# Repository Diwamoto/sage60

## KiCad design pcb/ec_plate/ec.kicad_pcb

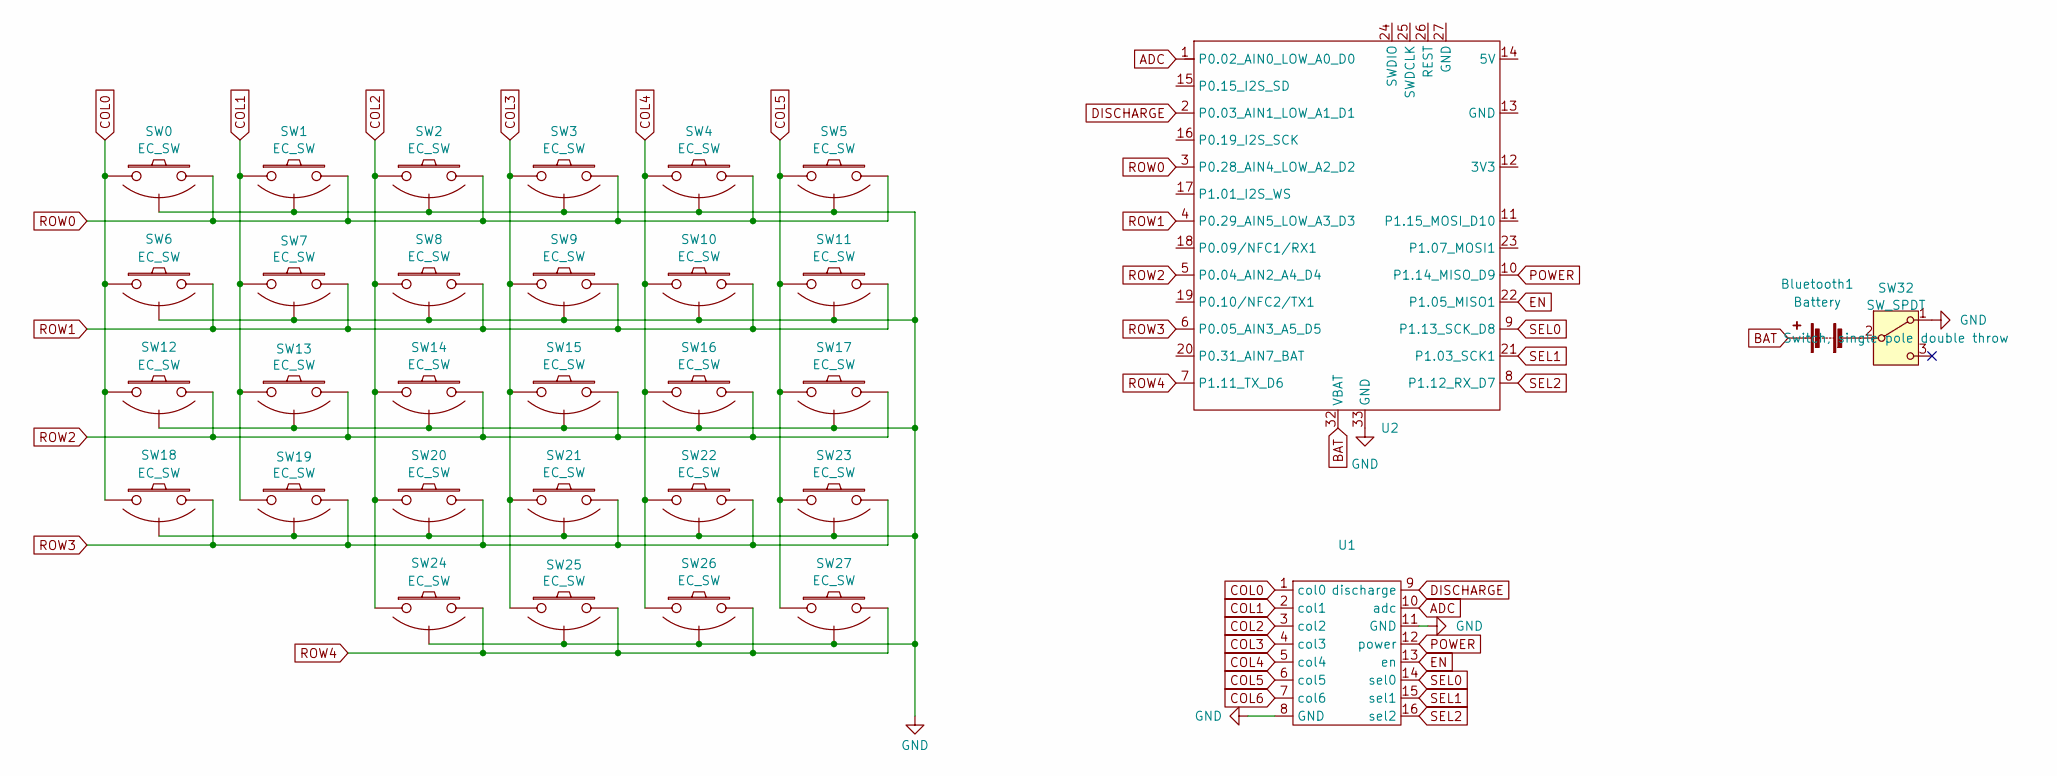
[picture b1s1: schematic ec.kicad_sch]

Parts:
Bluetooth1: Battery
SW0, SW1, SW2, SW3, SW4, SW5, SW6, SW7, SW8, SW9, SW10, SW11, SW12, SW13, SW14, SW15, SW16, SW17, SW18, SW19, SW20, SW21, SW22, SW23, SW24, SW25, SW26, SW27: EC_SW; ecs_pad_1U_no_ring
SW32: SW_SPDT; PinHeader_1x03_P2.54mm_Vertical
U1: ec_scan_module
U2: XIAO-nRF52840-Plus-DIP

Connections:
ADC: U1.10 (adc), U2.1 (P0.02_AIN0_LOW_A0_D0); also elsewhere on the board
COL0: SW0.1, SW6.1, SW12.1, SW18.1, U1.1 (col0)
COL1: SW1.1, SW7.1, SW13.1, SW19.1, U1.2 (col1)
COL2: SW2.1, SW8.1, SW14.1, SW20.1, SW24.1, U1.3 (col2)
COL3: SW3.1, SW9.1, SW15.1, SW21.1, SW25.1, U1.4 (col3)
COL4: SW4.1, SW10.1, SW16.1, SW22.1, SW26.1, U1.5 (col4)
COL5: SW5.1, SW11.1, SW17.1, SW23.1, SW27.1, U1.6 (col5)
COL6: U1.7 (col6)
DISCHARGE: U1.9 (discharge), U2.2 (P0.03_AIN1_LOW_A1_D1); also elsewhere on the board
EN: U1.13 (en), U2.22 (P1.05_MISO1); also elsewhere on the board
GND: SW0.3 (SG), SW1.3 (SG), SW2.3 (SG), SW3.3 (SG), SW4.3 (SG), SW5.3 (SG), SW6.3 (SG), SW7.3 (SG), SW8.3 (SG), SW9.3 (SG), SW10.3 (SG), SW11.3 (SG), SW12.3 (SG), SW13.3 (SG), SW14.3 (SG), SW15.3 (SG), SW16.3 (SG), SW17.3 (SG), SW18.3 (SG), SW19.3 (SG), SW20.3 (SG), SW21.3 (SG), SW22.3 (SG), SW23.3 (SG), SW24.3 (SG), SW25.3 (SG), SW26.3 (SG), SW27.3 (SG), SW32.1 (A), U1.8 (GND), U1.11 (GND), U2.33 (GND); also elsewhere on the board
unnamed: Bluetooth1.1 (+), U2.32 (VBAT)
unnamed: Bluetooth1.2 (-), SW32.2 (B)
POWER: U1.12 (power), U2.10 (P1.14_MISO_D9); also elsewhere on the board
ROW0: SW0.2, SW1.2, SW2.2, SW3.2, SW4.2, SW5.2, U2.3 (P0.28_AIN4_LOW_A2_D2); also elsewhere on the board
ROW1: SW6.2, SW7.2, SW8.2, SW9.2, SW10.2, SW11.2, U2.4 (P0.29_AIN5_LOW_A3_D3); also elsewhere on the board
ROW2: SW12.2, SW13.2, SW14.2, SW15.2, SW16.2, SW17.2, U2.5 (P0.04_AIN2_A4_D4); also elsewhere on the board
ROW3: SW18.2, SW19.2, SW20.2, SW21.2, SW22.2, SW23.2, U2.6 (P0.05_AIN3_A5_D5); also elsewhere on the board
ROW4: SW24.2, SW25.2, SW26.2, SW27.2, U2.7 (P1.11_TX_D6); also elsewhere on the board
SEL0: U1.14 (sel0), U2.9 (P1.13_SCK_D8); also elsewhere on the board
SEL1: U1.15 (sel1), U2.21 (P1.03_SCK1); also elsewhere on the board
SEL2: U1.16 (sel2), U2.8 (P1.12_RX_D7); also elsewhere on the board

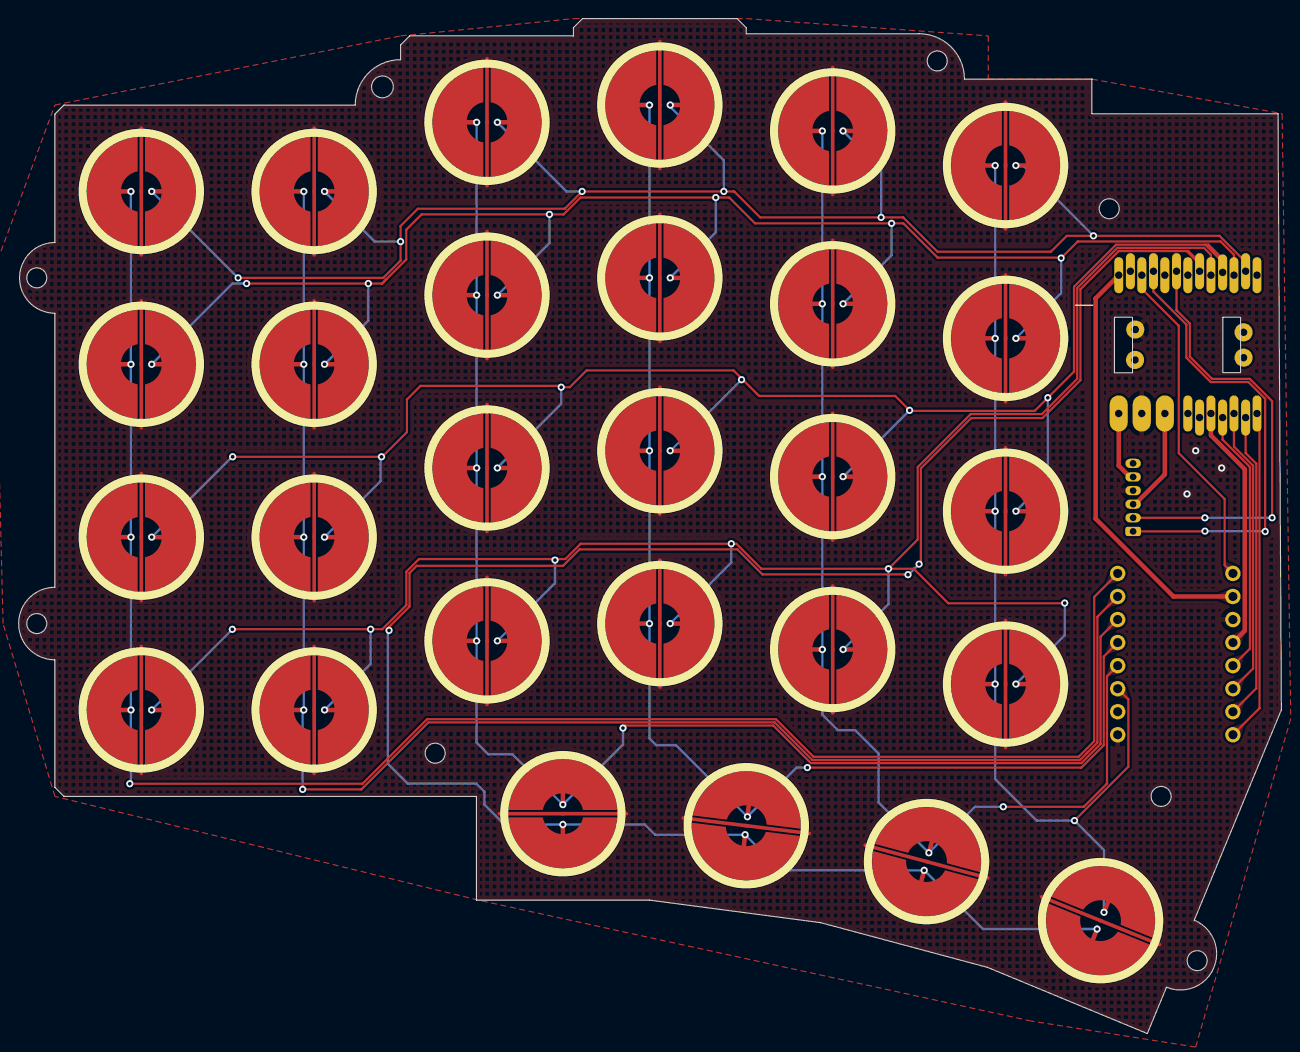
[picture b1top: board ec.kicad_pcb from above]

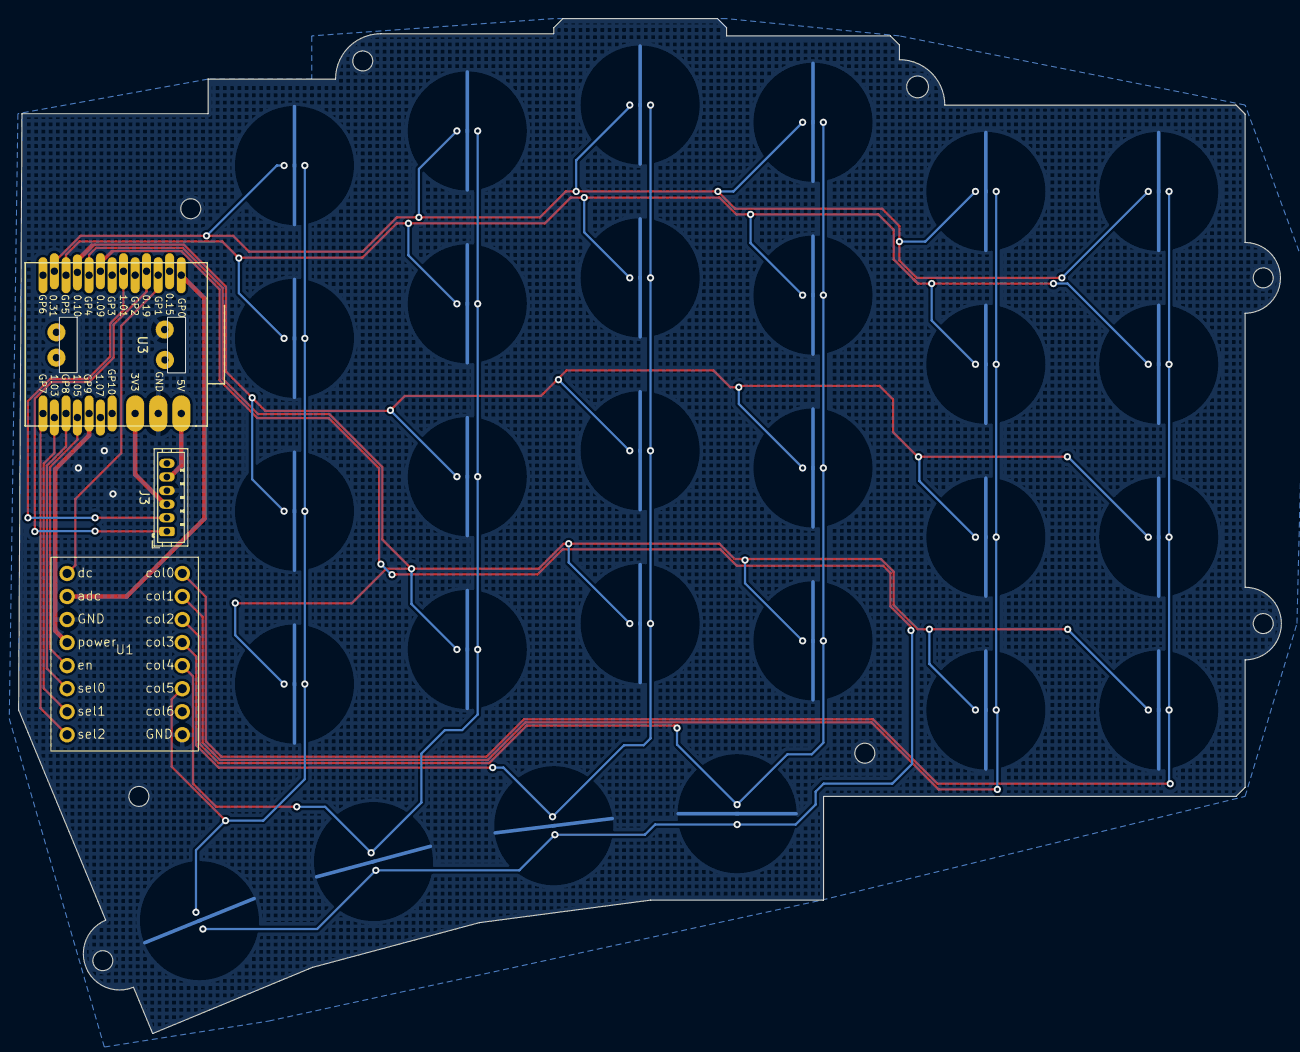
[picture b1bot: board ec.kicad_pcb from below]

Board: 2 copper layers, 139.2 x 111.9 mm, 31 parts (2 on the bottom side), 23 nets.

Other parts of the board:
J3: Conn_01x06_Socket; JST_ZH_B6B-ZR_1x06_P1.50mm_Vertical
U3: XIAO_nRF52840_plus_mki

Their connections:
+3.3V: J3.3, U3.12 (3V3)
ADC: U3.1 (P0.02_AIN0_LOW_A0_D0); also elsewhere on the board
DISCHARGE: U3.2 (P0.03_AIN1_LOW_A1_D1); also elsewhere on the board
EN: U3.24 (SWDIO); also elsewhere on the board
GND: J3.4, U3.13 (GND), U3.27 (GND); also elsewhere on the board
POWER: U3.10 (P1.14_MISO_D9); also elsewhere on the board
ROW0: U3.22 (P1.05_MISO1); also elsewhere on the board
ROW1: U3.6 (P0.05_AIN3_A5_D5); also elsewhere on the board
ROW2: U3.21 (P1.03_SCK1); also elsewhere on the board
ROW3: U3.5 (P0.04_AIN2_A4_D4); also elsewhere on the board
ROW4: U3.20 (P0.31_AIN7_BAT); also elsewhere on the board
RX: J3.1, U3.18 (P0.09/NFC1/RX1)
SEL0: U3.9 (P1.13_SCK_D8); also elsewhere on the board
SEL1: U3.25 (SWDCLK); also elsewhere on the board
SEL2: U3.8 (P1.12_RX_D7); also elsewhere on the board
TX: J3.2, U3.19 (P0.10/NFC2/TX1)
VBAT: J3.5, U3.14 (5V)

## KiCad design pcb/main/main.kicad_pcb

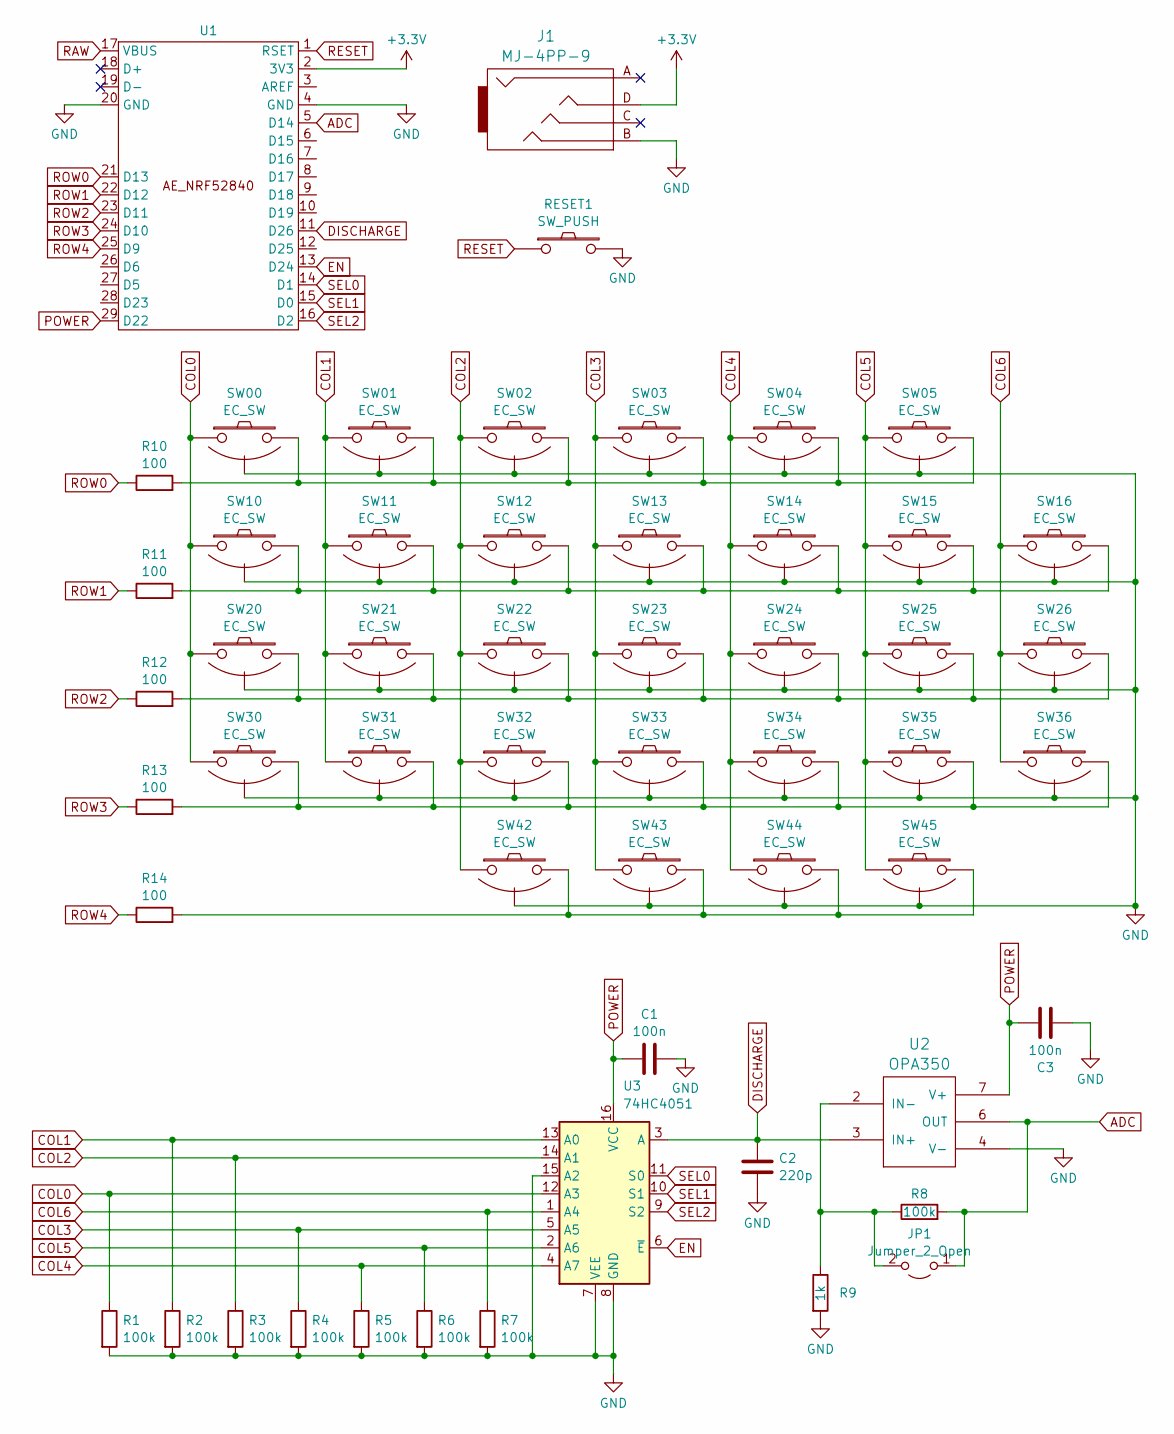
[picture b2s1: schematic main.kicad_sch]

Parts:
C1, C3: 100n; C_0805_2012Metric_Pad1.18x1.45mm_HandSolder
C2: 220p; C_0805_2012Metric_Pad1.18x1.45mm_HandSolder
J1: MJ-4PP-9; MJ-4PP-9_1side
JP1: Jumper_2_Open; R_0805_2012Metric_Pad1.20x1.40mm_HandSolder
R1, R2, R3, R4, R5, R6, R7, R8: 100k; R_0805_2012Metric_Pad1.20x1.40mm_HandSolder
R9: 1k; R_0805_2012Metric_Pad1.20x1.40mm_HandSolder
R10, R11, R12, R13, R14: 100; R_0805_2012Metric_Pad1.20x1.40mm_HandSolder
RESET1: SW_PUSH; ResetSW_1side
SW00, SW01, SW02, SW03, SW04, SW05, SW10, SW11, SW12, SW13, SW14, SW15, SW16, SW20, SW21, SW22, SW23, SW24, SW25, SW26, SW30, SW31, SW32, SW33, SW34, SW35, SW36, SW42, SW43, SW44, SW45: EC_SW; ecs_pad_1U_no_ring_90deg
U1: ae_nrf52840
U2: OPA350; SOIC-8_3.9x4.9mm_P1.27mm
U3: 74HC4051; SOIC-16_3.9x9.9mm_P1.27mm

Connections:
+3.3V: J1.D, U1.2 (3V3)
ADC: JP1.1 (A), R8.2, U1.5 (D14), U2.6 (OUT)
COL0: R1.1, SW00.1, SW10.1, SW20.1, SW30.1, U3.12 (A3)
COL1: R2.1, SW01.1, SW11.1, SW21.1, SW31.1, U3.13 (A0)
COL2: R3.1, SW02.1, SW12.1, SW22.1, SW32.1, SW42.1, U3.14 (A1)
COL3: R4.1, SW03.1, SW13.1, SW23.1, SW33.1, SW43.1, U3.5 (A5)
COL4: R5.1, SW04.1, SW14.1, SW24.1, SW34.1, SW44.1, U3.4 (A7)
COL5: R6.1, SW05.1, SW15.1, SW25.1, SW35.1, SW45.1, U3.2 (A6)
COL6: R7.1, SW16.1, SW26.1, SW36.1, U3.1 (A4)
DISCHARGE: C2.2, U1.11 (D26), U2.3 (IN+), U3.3 (A)
EN: U1.13 (D24), U3.6 (~E)
GND: C1.2, C2.1, C3.1, J1.B, R1.2, R2.2, R3.2, R4.2, R5.2, R6.2, R7.2, R9.2, RESET1.2, SW00.3 (SG), SW01.3 (SG), SW02.3 (SG), SW03.3 (SG), SW04.3 (SG), SW05.3 (SG), SW10.3 (SG), SW11.3 (SG), SW12.3 (SG), SW13.3 (SG), SW14.3 (SG), SW15.3 (SG), SW16.3 (SG), SW20.3 (SG), SW21.3 (SG), SW22.3 (SG), SW23.3 (SG), SW24.3 (SG), SW25.3 (SG), SW26.3 (SG), SW30.3 (SG), SW31.3 (SG), SW32.3 (SG), SW33.3 (SG), SW34.3 (SG), SW35.3 (SG), SW36.3 (SG), SW42.3 (SG), SW43.3 (SG), SW44.3 (SG), SW45.3 (SG), U1.4 (GND), U1.20 (GND), U2.4 (V-), U3.7 (VEE), U3.8 (GND), U3.15 (A2)
unnamed: JP1.2 (B), R8.1, R9.1, U2.2 (IN-)
unnamed: R10.2, SW00.2, SW01.2, SW02.2, SW03.2, SW04.2, SW05.2
unnamed: R11.2, SW10.2, SW11.2, SW12.2, SW13.2, SW14.2, SW15.2, SW16.2
unnamed: R12.2, SW20.2, SW21.2, SW22.2, SW23.2, SW24.2, SW25.2, SW26.2
unnamed: R13.2, SW30.2, SW31.2, SW32.2, SW33.2, SW34.2, SW35.2, SW36.2
unnamed: R14.2, SW42.2, SW43.2, SW44.2, SW45.2
POWER: C1.1, C3.2, U1.29 (D22), U2.7 (V+), U3.16 (VCC)
RAW: U1.17 (VBUS)
RESET: RESET1.1, U1.1 (RSET)
ROW0: R10.1, U1.21 (D13)
ROW1: R11.1, U1.22 (D12)
ROW2: R12.1, U1.23 (D11)
ROW3: R13.1, U1.24 (D10)
ROW4: R14.1, U1.25 (D9)
SEL0: U1.14 (D1), U3.11 (S0)
SEL1: U1.15 (D0), U3.10 (S1)
SEL2: U1.16 (D2), U3.9 (S2)

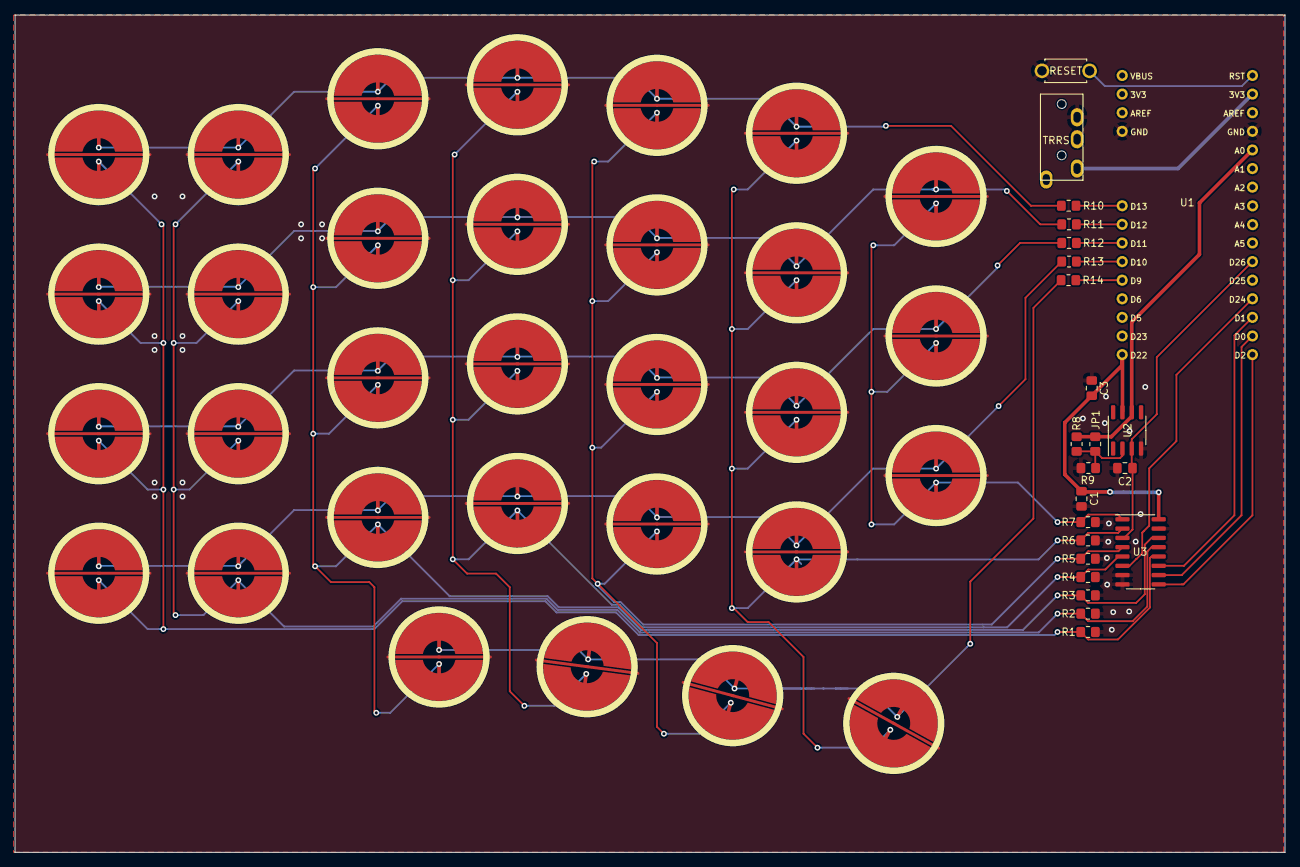
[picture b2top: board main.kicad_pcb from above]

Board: 2 copper layers, 173.4 x 114.3 mm, 54 parts (0 on the bottom side), 28 nets.

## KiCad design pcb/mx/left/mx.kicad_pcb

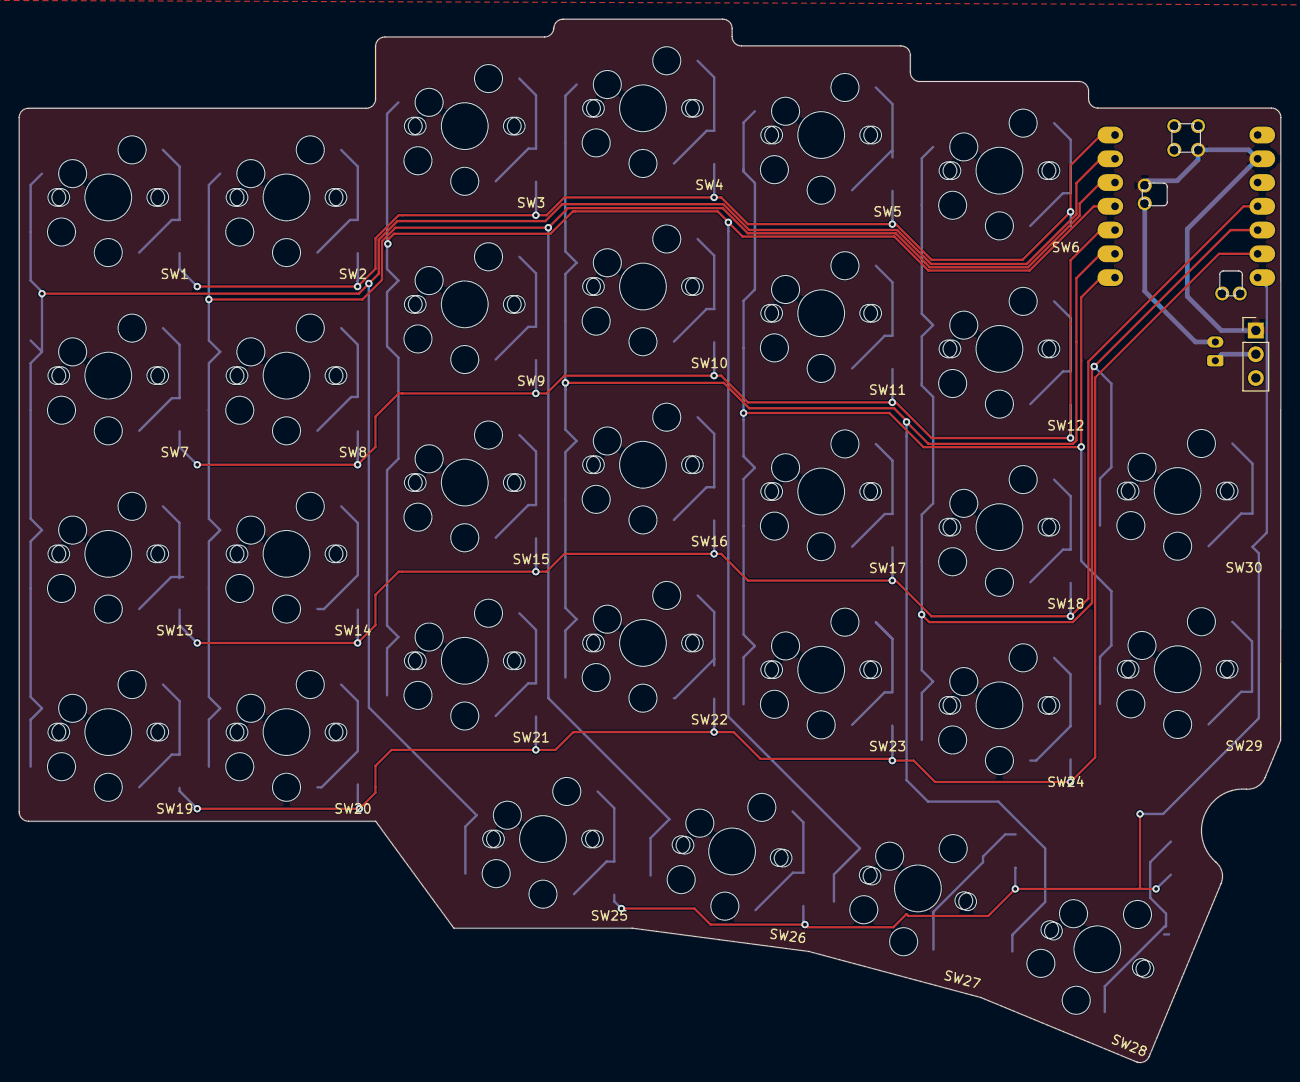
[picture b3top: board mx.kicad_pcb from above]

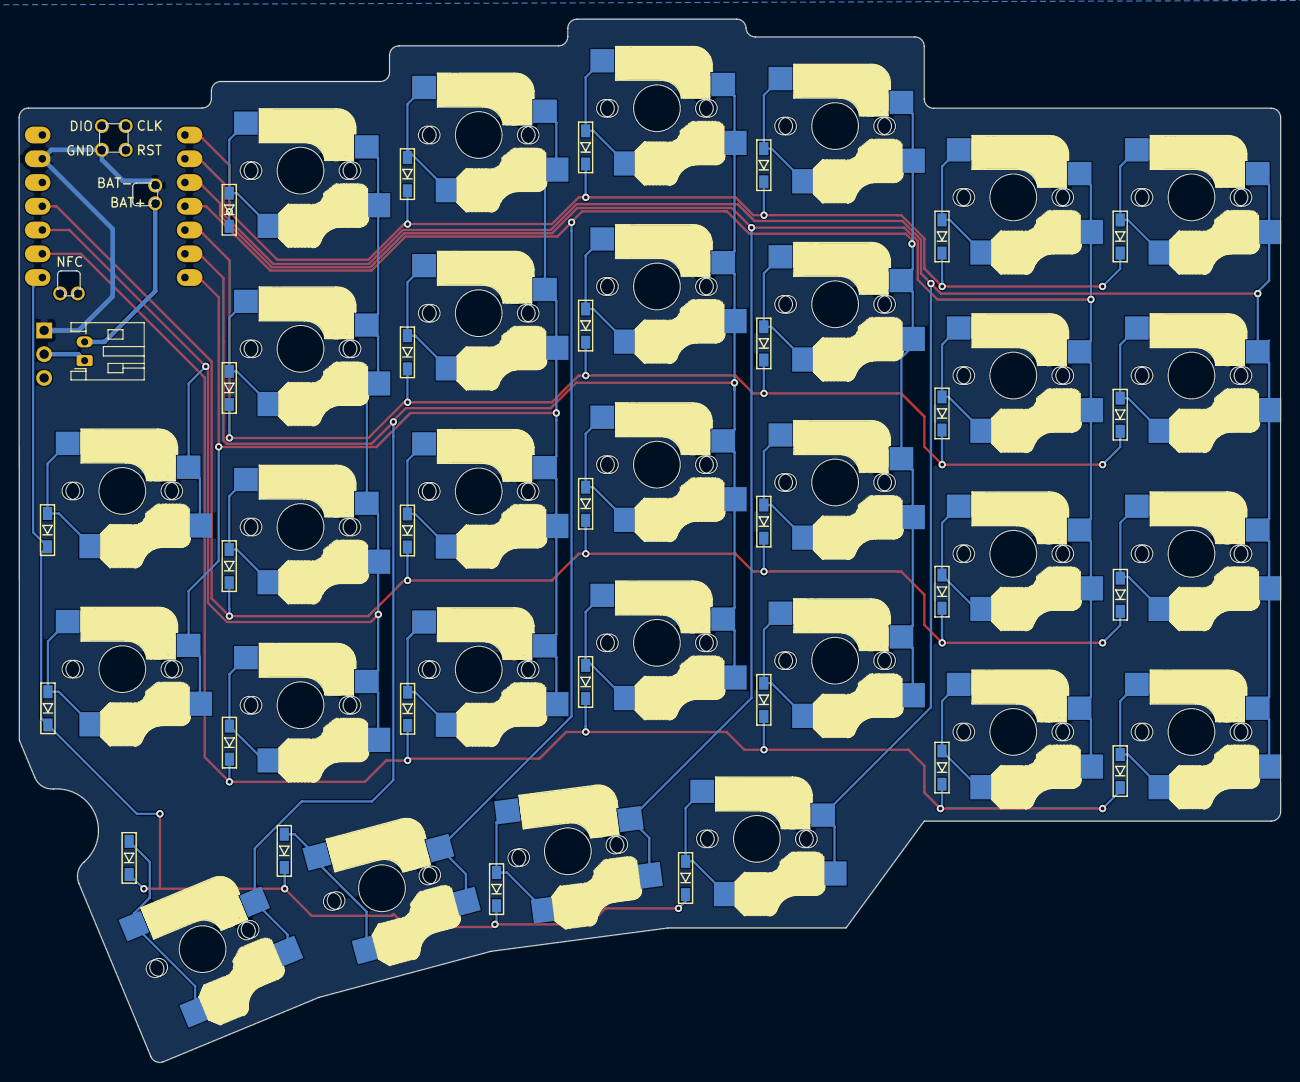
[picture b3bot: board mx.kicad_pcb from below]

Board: 2 copper layers, 134.9 x 111.5 mm, 63 parts (31 on the bottom side), 44 nets.

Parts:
Bluetooth1: Battery; JST_PH_S2B-PH-K_custom
D1, D2, D3, D4, D5, D6, D7, D8, D9, D10, D11, D12, D13, D14, D15, D16, D17, D18, D19, D20, D21, D22, D23, D24, D25, D26, D27, D28, D29, D30: D; D3_SMD_v2
SW1, SW2, SW3, SW4, SW5, SW6, SW7, SW8, SW9, SW10, SW11, SW12, SW13, SW14, SW15, SW16, SW17, SW18, SW19, SW20, SW21, SW22, SW23, SW24, SW25, SW26, SW27, SW28, SW29, SW30: SW_PUSH; CherryMX_Choc_Hotswap_v2
SW32: SW_SPDT; PinHeader_1x03_P2.54mm_Vertical
U1: XIAO_nRF52840

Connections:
BAT: Bluetooth1.1 (+), U1.21 (BATT-)
COL0: SW1.1, SW7.1, SW13.1, SW19.1, SW25.1, U1.2 (P0.03_A1_D1)
COL1: SW2.1, SW8.1, SW14.1, SW20.1, SW26.1, U1.3 (P0.28_A2_D2)
COL2: SW3.1, SW9.1, SW15.1, SW21.1, SW27.1, U1.4 (P0.29_A3_D3)
COL3: SW4.1, SW10.1, SW16.1, SW22.1, SW28.1, U1.6 (P0.05_A5_D5_SCL)
COL4: SW5.1, SW11.1, SW17.1, SW23.1, SW29.1, U1.7 (P1.11_D6_TX)
COL5: SW6.1, SW12.1, SW18.1, SW24.1, SW30.1, U1.10 (P1.14_D9_MISO)
GND: SW32.1 (A), U1.13 (GND), U1.18 (NFC4_1.00), U1.22 (RST)
unnamed: Bluetooth1.2 (-), SW32.2 (B)
unnamed: D1.2 (A), SW1.2
unnamed: D2.2 (A), SW2.2
unnamed: D3.2 (A), SW3.2
unnamed: D4.2 (A), SW4.2
unnamed: D5.2 (A), SW5.2
unnamed: D6.2 (A), SW6.2
unnamed: D7.2 (A), SW7.2
unnamed: D8.2 (A), SW8.2
unnamed: D9.2 (A), SW9.2
unnamed: D10.2 (A), SW10.2
unnamed: D11.2 (A), SW11.2
unnamed: D12.2 (A), SW12.2
unnamed: D13.2 (A), SW13.2
unnamed: D14.2 (A), SW14.2
unnamed: D15.2 (A), SW15.2
unnamed: D16.2 (A), SW16.2
unnamed: D17.2 (A), SW17.2
unnamed: D18.2 (A), SW18.2
unnamed: D19.2 (A), SW19.2
unnamed: D20.2 (A), SW20.2
unnamed: D21.2 (A), SW21.2
unnamed: D22.2 (A), SW22.2
unnamed: D23.2 (A), SW23.2
unnamed: D24.2 (A), SW24.2
unnamed: D25.2 (A), SW25.2
unnamed: D26.2 (A), SW26.2
unnamed: D27.2 (A), SW27.2
unnamed: D28.2 (A), SW28.2
unnamed: D29.2 (A), SW29.2
unnamed: D30.2 (A), SW30.2
ROW0: D1.1 (K), D2.1 (K), D3.1 (K), D4.1 (K), D5.1 (K), D6.1 (K), U1.1 (P0.02_A0_D0)
ROW1: D7.1 (K), D8.1 (K), D9.1 (K), D10.1 (K), D11.1 (K), D12.1 (K), U1.5 (P0.04_A4_D4_SDA)
ROW2: D13.1 (K), D14.1 (K), D15.1 (K), D16.1 (K), D17.1 (K), D18.1 (K), U1.11 (P1.15_D10_MOSI)
ROW3: D19.1 (K), D20.1 (K), D21.1 (K), D22.1 (K), D23.1 (K), D24.1 (K), U1.9 (P1.13_D8_SCK)
ROW4: D25.1 (K), D26.1 (K), D27.1 (K), D28.1 (K), D29.1 (K), D30.1 (K), U1.8 (P1.12_D7_RX)
